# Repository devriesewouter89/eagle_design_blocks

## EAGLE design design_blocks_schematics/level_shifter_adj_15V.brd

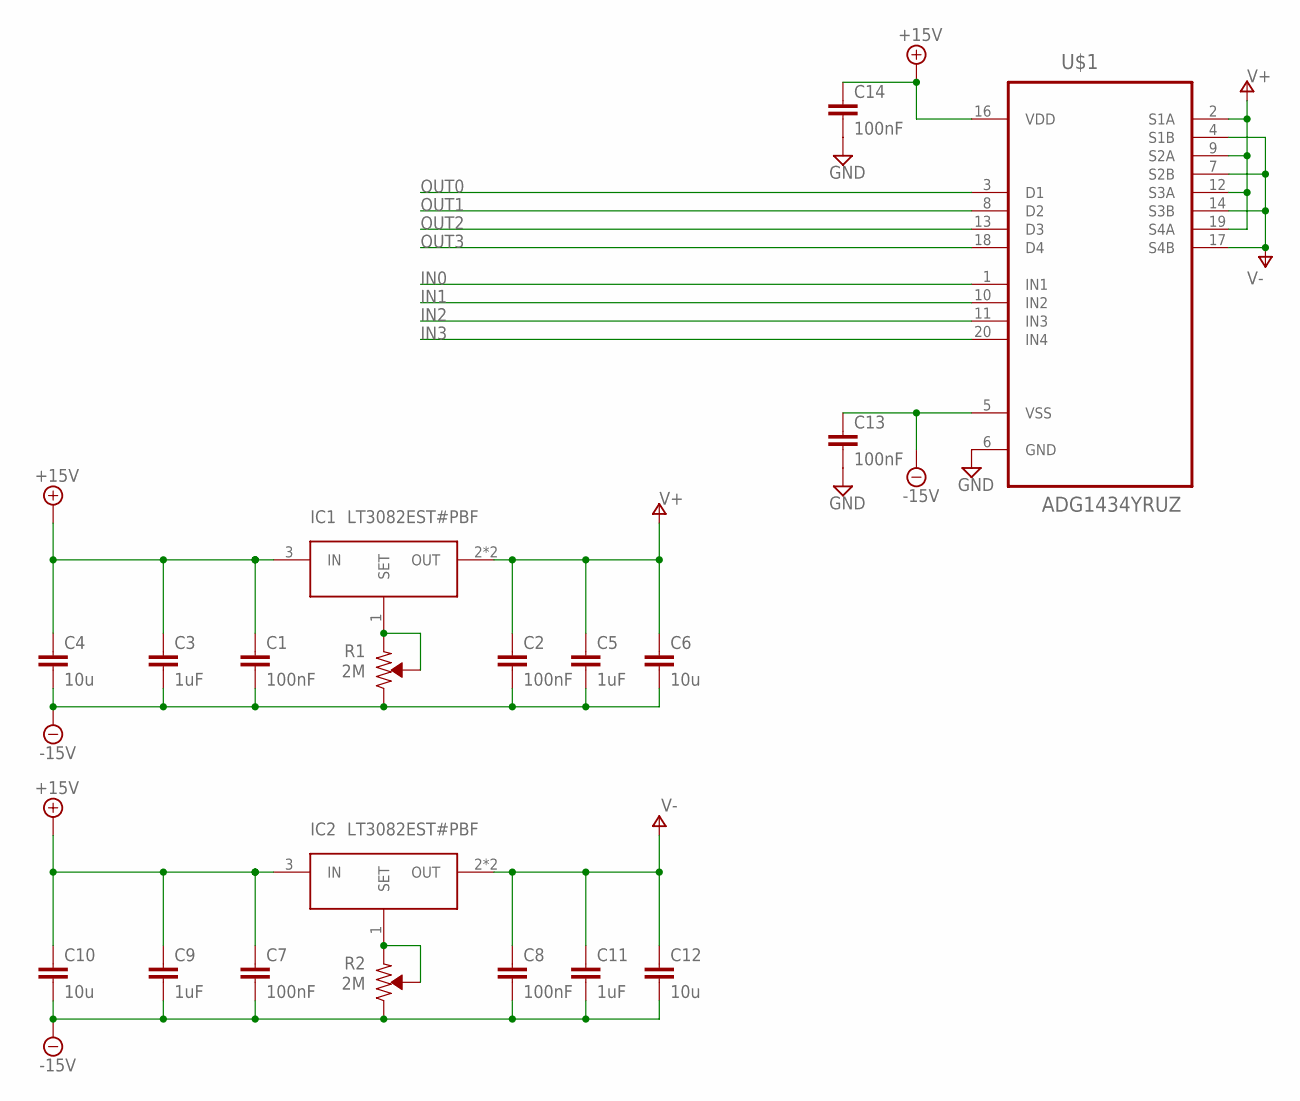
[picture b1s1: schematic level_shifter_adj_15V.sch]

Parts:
C1, C2, C7, C8, C13, C14: 100nF; C0402
C3, C5, C9, C11: 1uF; C0402; VOLTAGERATING 25V
C4, C6, C10, C12: 10u; C0603; VOLTAGERATING 25V
IC1, IC2: LT3082EST#PBF; SOT230P700X180-4N
R1, R2: 2M; TRIM_3296Y-1-202LF
U$1: ADG1434YRUZ; SOP65P640X120-20N

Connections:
+15V: C1.1, C3.1, C4.1, C7.1, C9.1, C10.1, C14.1, IC1.3 (IN), IC2.3 (IN), U$1.16 (VDD)
-15V: C1.2, C2.2, C3.2, C4.2, C5.2, C6.2, C7.2, C8.2, C9.2, C10.2, C11.2, C12.2, C13.1, R1.3 (CW), R2.3 (CW), U$1.5 (VSS)
GND: C13.2, C14.2, U$1.6 (GND)
IN0: U$1.1 (IN1)
IN1: U$1.10 (IN2)
IN2: U$1.11 (IN3)
IN3: U$1.20 (IN4)
unnamed: IC2.1 (SET), R2.1 (CCW), R2.2 (WIPER)
unnamed: IC1.1 (SET), R1.1 (CCW), R1.2 (WIPER)
OUT0: U$1.3 (D1)
OUT1: U$1.8 (D2)
OUT2: U$1.13 (D3)
OUT3: U$1.18 (D4)
V+: C2.1, C5.1, C6.1, IC1.2 (OUT), IC1.4 (OUT), U$1.2 (S1A), U$1.9 (S2A), U$1.12 (S3A), U$1.19 (S4A)
V-: C8.1, C11.1, C12.1, IC2.2 (OUT), IC2.4 (OUT), U$1.4 (S1B), U$1.7 (S2B), U$1.14 (S3B), U$1.17 (S4B)

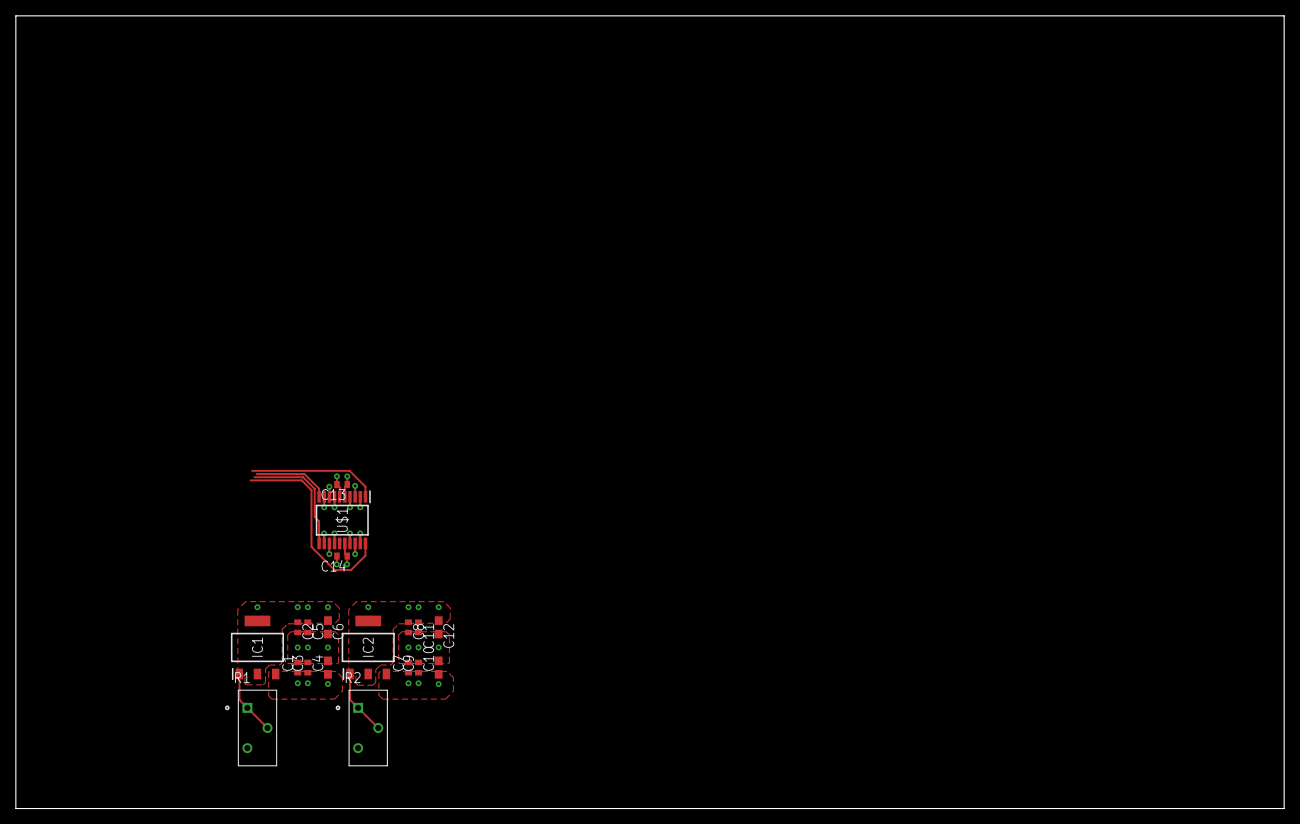
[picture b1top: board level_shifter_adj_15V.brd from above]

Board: 2 copper layers, 160.0 x 100.0 mm, 19 parts (0 on the bottom side), 7 nets.

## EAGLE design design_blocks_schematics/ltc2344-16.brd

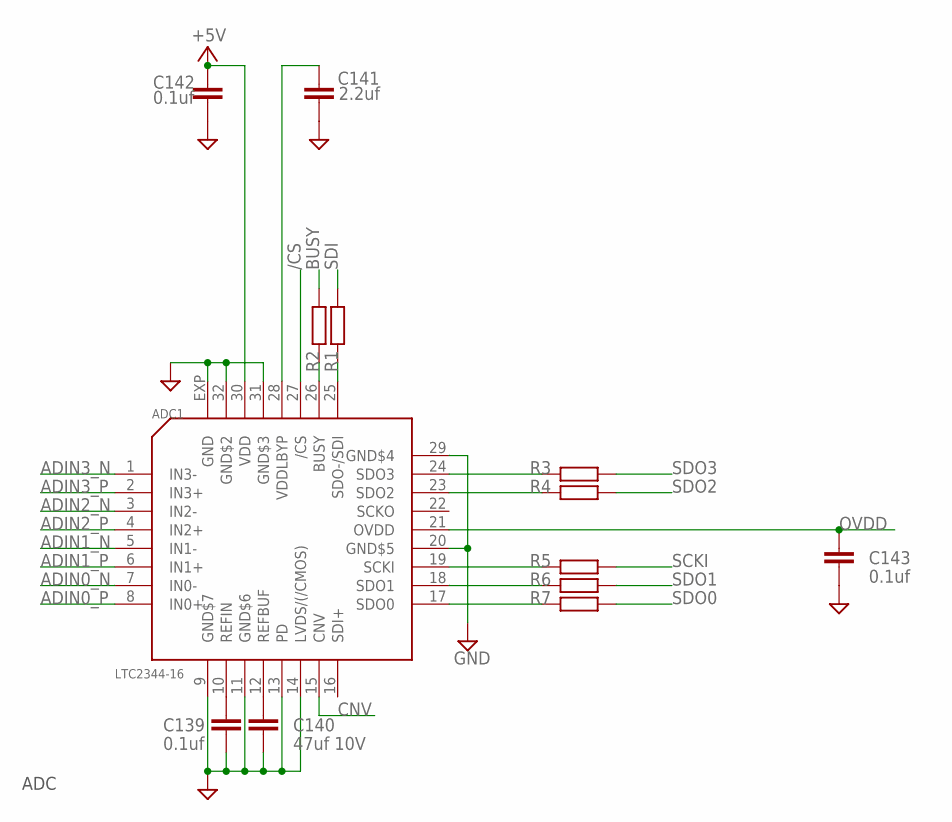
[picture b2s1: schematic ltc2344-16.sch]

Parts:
ADC1: LTC2344-16; QFN32
C139, C142, C143: 0.1uf; C0402
C140: 47uf 10V; C1210
C141: 2.2uf; C0402
R1, R2, R3, R4, R5, R6, R7: 33R; R0402

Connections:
+5V: ADC1.30 (VDD), C142.1
/CS: ADC1.27 (/CS)
ADIN0_N: ADC1.7 (IN0-)
ADIN0_P: ADC1.8 (IN0+)
ADIN1_N: ADC1.5 (IN1-)
ADIN1_P: ADC1.6 (IN1+)
ADIN2_N: ADC1.3 (IN2-)
ADIN2_P: ADC1.4 (IN2+)
ADIN3_N: ADC1.1 (IN3-)
ADIN3_P: ADC1.2 (IN3+)
BUSY: R2.2
CNV: ADC1.15 (CNV)
GND: ADC1.9 (GND$7), ADC1.11 (GND$6), ADC1.13 (PD), ADC1.14 (LVDS/(/CMOS)), ADC1.20 (GND$5), ADC1.29 (GND$4), ADC1.31 (GND$3), ADC1.32 (GND$2), ADC1.EXP (GND), C139.2, C140.2, C141.2, C142.2, C143.2
N1: ADC1.26 (BUSY), R2.1
N2: ADC1.25 (SDO-/SDI), R1.1
unnamed: ADC1.24 (SDO3), R3.2
unnamed: ADC1.23 (SDO2), R4.2
unnamed: ADC1.19 (SCKI), R5.2
unnamed: ADC1.18 (SDO1), R6.2
unnamed: ADC1.17 (SDO0), R7.2
unnamed: ADC1.10 (REFIN), C139.1
unnamed: ADC1.12 (REFBUF), C140.1
unnamed: ADC1.28 (VDDLBYP), C141.1
OVDD: ADC1.21 (OVDD), C143.1
SCKI: R5.1
SDI: R1.2
SDO0: R7.1
SDO1: R6.1
SDO2: R4.1
SDO3: R3.1

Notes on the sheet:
ADC

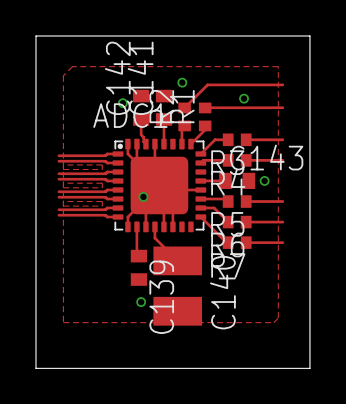
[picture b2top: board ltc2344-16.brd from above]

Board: 4 copper layers, 15.2 x 18.5 mm, 13 parts (0 on the bottom side), 13 nets.

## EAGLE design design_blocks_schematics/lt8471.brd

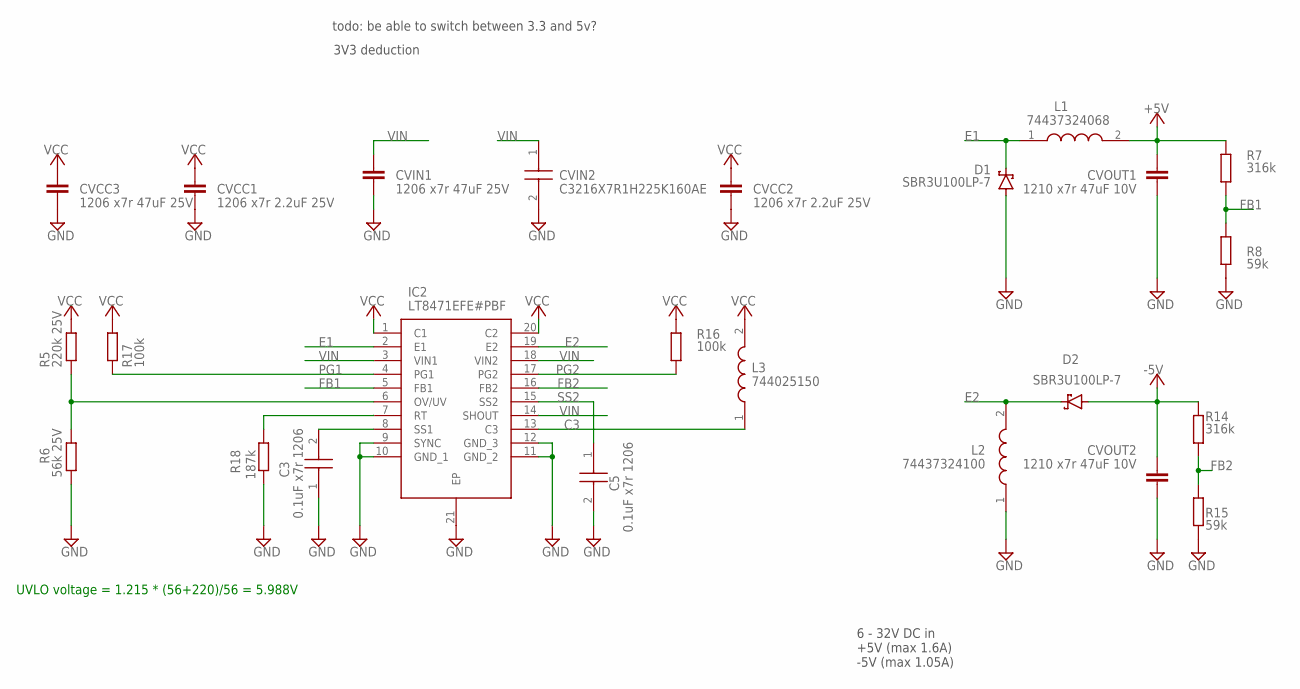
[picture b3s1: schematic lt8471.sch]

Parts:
C3, C5: 0.1uF x7r 1206; CAPC3416X90N
CVCC1, CVCC2: 1206 x7r 2.2uF 25V; C1206
CVCC3: 1206 x7r 47uF 25V; C1210
CVIN1: 1206 x7r 47uF 25V; C1210
CVIN2: C3216X7R1H225K160AE; CAPC3216X180N
CVOUT1, CVOUT2: 1210 x7r 47uF 10V; C1210
D1, D2: SBR3U100LP-7; SBR3U100LP7
IC2: LT8471EFE#PBF; SOP65P640X120-21N
L1: 74437324068; WE-LHMI_402048
L2: 74437324100; WE-LHMI_402048
L3: 744025150; WE-TPC_282892
R5: 220k 25V; M1206
R6: 56k 25V; M1206
R7, R14: 316k; R1206
R8, R15: 59k; R1206
R16, R17: 100k; R1206
R18: 187k; R1206

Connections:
+5V: CVOUT1.2, L1.2, R7.2
-5V: CVOUT2.2, D2.1 (A), D2.2 (A), D2.3 (A), D2.4 (A), R14.2
C3: IC2.13 (C3), L3.1
E1: D1.5 (C), IC2.2 (E1), L1.1
E2: D2.5 (C), IC2.19 (E2), L2.2
FB1: IC2.5 (FB1), R7.1, R8.2
FB2: IC2.16 (FB2), R14.1, R15.2
GND: C3.1, C5.2, CVCC1.2, CVCC2.1, CVCC3.1, CVIN1.2, CVIN2.2, CVOUT1.1, CVOUT2.1, D1.1 (A), D1.2 (A), D1.3 (A), D1.4 (A), IC2.9 (SYNC), IC2.10 (GND_1), IC2.11 (GND_2), IC2.12 (GND_3), IC2.21 (EP), L2.1, R6.1, R8.1, R15.1, R18.2
unnamed: IC2.7 (RT), R18.1
unnamed: IC2.6 (OV/UV), R5.1, R6.2
PG1: IC2.4 (PG1), R17.1
PG2: IC2.17 (PG2), R16.2
SS1: C3.2, IC2.8 (SS1)
SS2: C5.1, IC2.15 (SS2)
VCC: CVCC1.1, CVCC2.2, CVCC3.2, IC2.1 (C1), IC2.20 (C2), L3.2, R5.2, R16.1, R17.2
VIN: CVIN1.1, CVIN2.1, IC2.3 (VIN1), IC2.14 (SHOUT), IC2.18 (VIN2)

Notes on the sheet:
3V3 deduction
todo: be able to switch between 3.3 and 5v?
6 - 32V DC in +5V (max 1.6A) -5V (max 1.05A)
UVLO voltage = 1.215 * (56+220)/56 = 5.988V

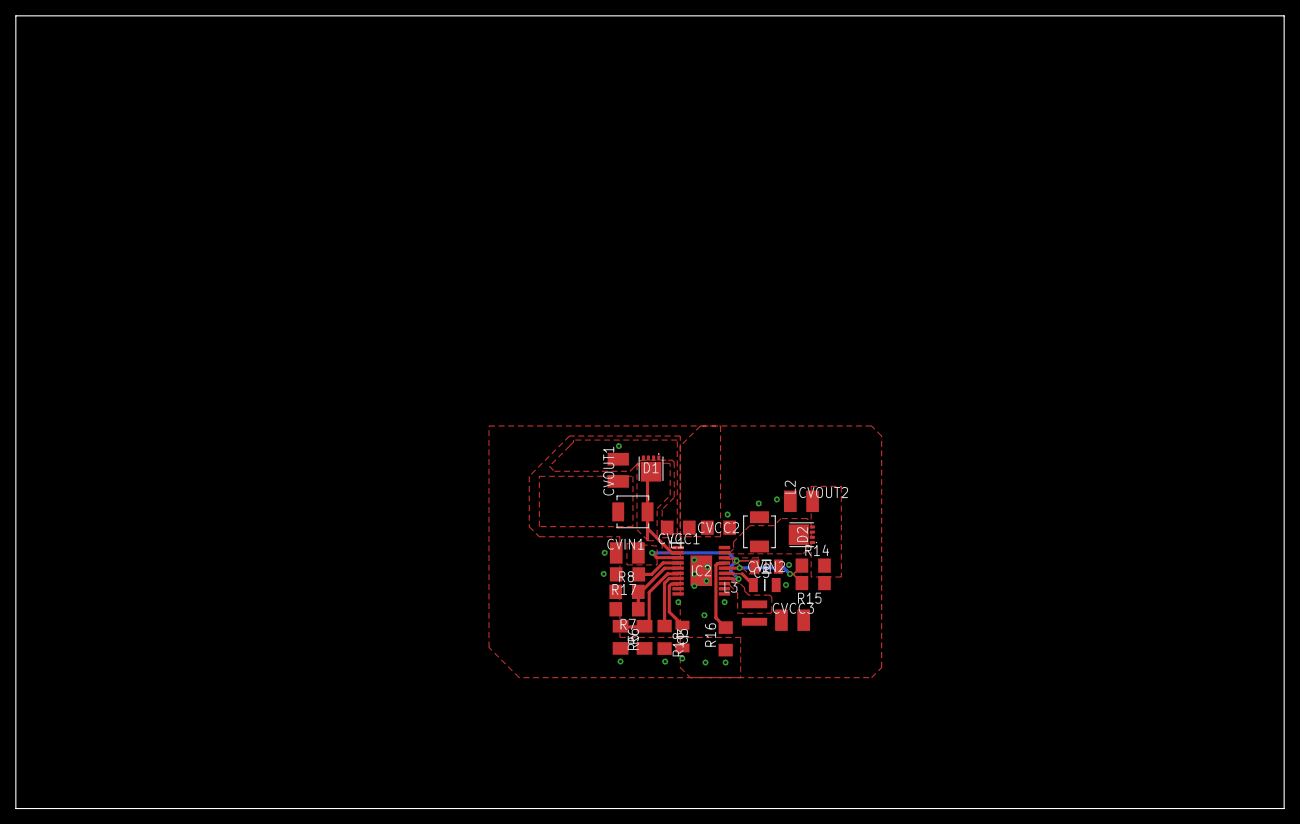
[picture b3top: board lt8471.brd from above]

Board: 2 copper layers, 160.0 x 100.0 mm, 24 parts (0 on the bottom side), 16 nets.

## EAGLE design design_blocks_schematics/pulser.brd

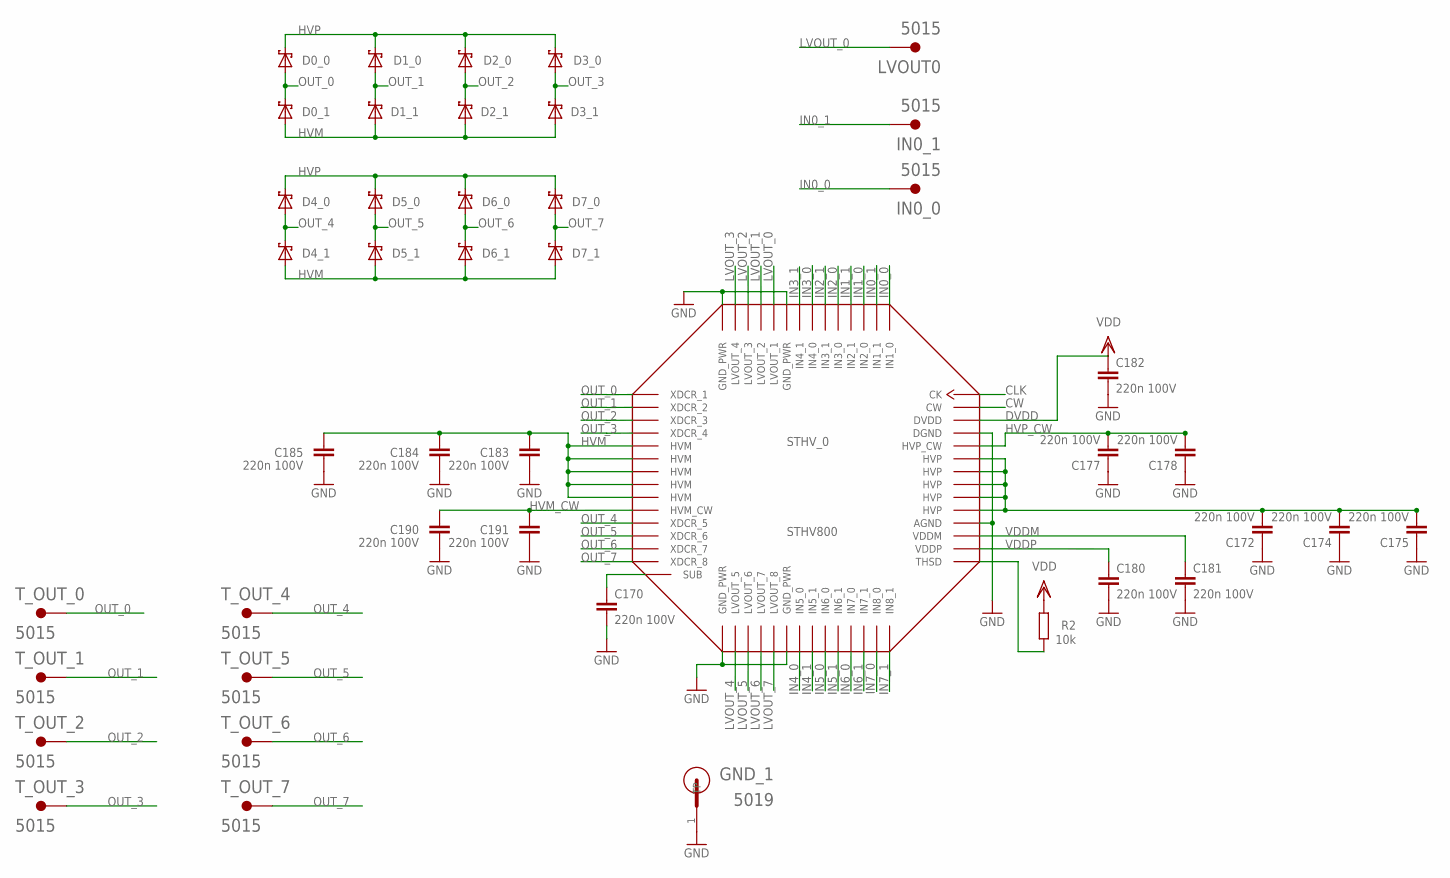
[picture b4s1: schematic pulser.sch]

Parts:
C170, C172, C174, C175, C177, C178, C180, C181, C182, C183, C184, C185, C190, C191: 220n 100V; C0805
D0_0, D0_1, D1_0, D1_1, D2_0, D2_1, D3_0, D3_1, D4_0, D4_1, D5_0, D5_1, D6_0, D6_1, D7_0, D7_1: SBR1U200P1SBR1U200P1; POWERDI-123
GND_1: 5019; TP380X203
IN0_0, IN0_1: 5015; KEYSTONE_5015
LVOUT0: 5015; KEYSTONE_5015
R2: 10k; R0805
STHV_0: STHV800; TFLGA-56LD
T_OUT_0, T_OUT_1, T_OUT_2, T_OUT_3, T_OUT_4, T_OUT_5, T_OUT_6, T_OUT_7: 5015; KEYSTONE_5015

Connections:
CLK: STHV_0.CK
CW: STHV_0.CW
GND: C170.2, C172.1, C174.1, C175.1, C177.1, C178.1, C180.2, C181.2, C182.2, C183.2, C184.2, C185.2, C190.1, C191.1, GND_1.1, STHV_0.AGND, STHV_0.DGND, STHV_0.GND_PWR@1 (GND_PWR), STHV_0.GND_PWR@2 (GND_PWR), STHV_0.GND_PWR@3 (GND_PWR), STHV_0.GND_PWR@4 (GND_PWR)
HVM: C183.1, C184.1, C185.1, D0_1.A, D1_1.A, D2_1.A, D3_1.A, D4_1.A, D5_1.A, D6_1.A, D7_1.A, STHV_0.HVM@1 (HVM), STHV_0.HVM@2 (HVM), STHV_0.HVM@3 (HVM), STHV_0.HVM@4 (HVM), STHV_0.HVM@5 (HVM)
HVM_CW: C190.2, C191.2, STHV_0.HVM_CW
HVP: C172.2, C174.2, C175.2, D0_0.C, D1_0.C, D2_0.C, D3_0.C, D4_0.C, D5_0.C, D6_0.C, D7_0.C, STHV_0.HVP@1 (HVP), STHV_0.HVP@2 (HVP), STHV_0.HVP@3 (HVP), STHV_0.HVP@4 (HVP), STHV_0.HVP@5 (HVP)
HVP_CW: C177.2, C178.2, STHV_0.HVP_CW
IN0_0: IN0_0.1, STHV_0.IN1_0
IN0_1: IN0_1.1, STHV_0.IN1_1
IN1_0: STHV_0.IN2_0
IN1_1: STHV_0.IN2_1
IN2_0: STHV_0.IN3_0
IN2_1: STHV_0.IN3_1
IN3_0: STHV_0.IN4_0
IN3_1: STHV_0.IN4_1
IN4_0: STHV_0.IN5_0
IN4_1: STHV_0.IN5_1
IN5_0: STHV_0.IN6_0
IN5_1: STHV_0.IN6_1
IN6_0: STHV_0.IN7_0
IN6_1: STHV_0.IN7_1
IN7_0: STHV_0.IN8_0
IN7_1: STHV_0.IN8_1
LVOUT_0: LVOUT0.1, STHV_0.LVOUT_1
LVOUT_1: STHV_0.LVOUT_2
LVOUT_2: STHV_0.LVOUT_3
LVOUT_3: STHV_0.LVOUT_4
LVOUT_4: STHV_0.LVOUT_5
LVOUT_5: STHV_0.LVOUT_6
LVOUT_6: STHV_0.LVOUT_7
LVOUT_7: STHV_0.LVOUT_8
unnamed: R2.1, STHV_0.THSD
unnamed: C170.1, STHV_0.SUB
OUT_0: D0_0.A, D0_1.C, STHV_0.XDCR_1, T_OUT_0.1
OUT_1: D1_0.A, D1_1.C, STHV_0.XDCR_2, T_OUT_1.1
OUT_2: D2_0.A, D2_1.C, STHV_0.XDCR_3, T_OUT_2.1
OUT_3: D3_0.A, D3_1.C, STHV_0.XDCR_4, T_OUT_3.1
OUT_4: D4_0.A, D4_1.C, STHV_0.XDCR_5, T_OUT_4.1
OUT_5: D5_0.A, D5_1.C, STHV_0.XDCR_6, T_OUT_5.1
OUT_6: D6_0.A, D6_1.C, STHV_0.XDCR_7, T_OUT_6.1
OUT_7: D7_0.A, D7_1.C, STHV_0.XDCR_8, T_OUT_7.1
VDDM: C181.1, STHV_0.VDDM

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
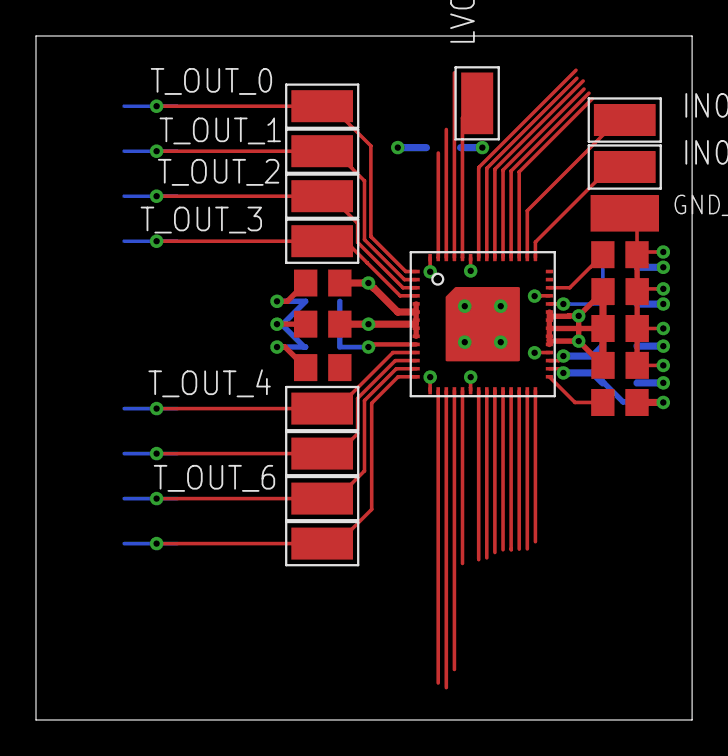
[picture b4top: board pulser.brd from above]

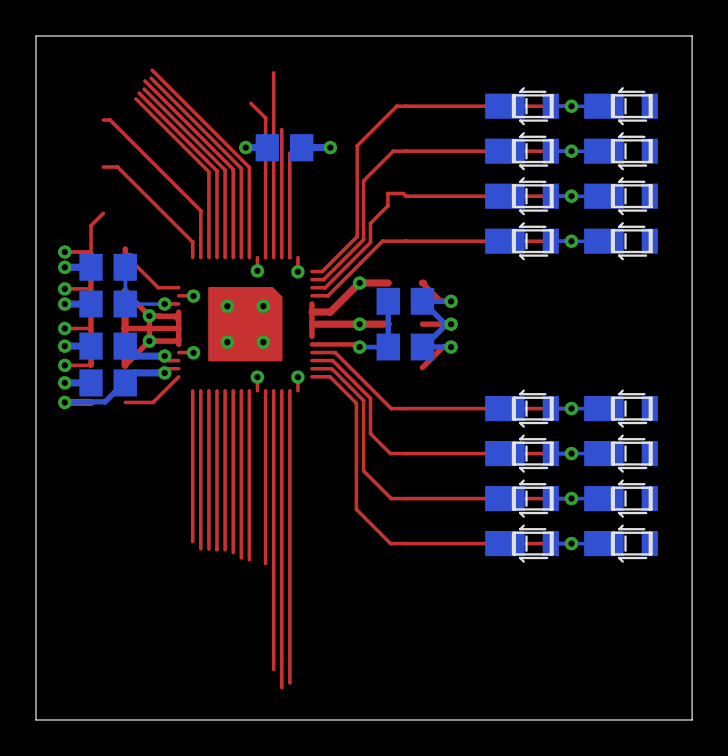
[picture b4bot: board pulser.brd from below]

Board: 2 copper layers, 36.5 x 38.0 mm, 44 parts (23 on the bottom side), 20 nets.

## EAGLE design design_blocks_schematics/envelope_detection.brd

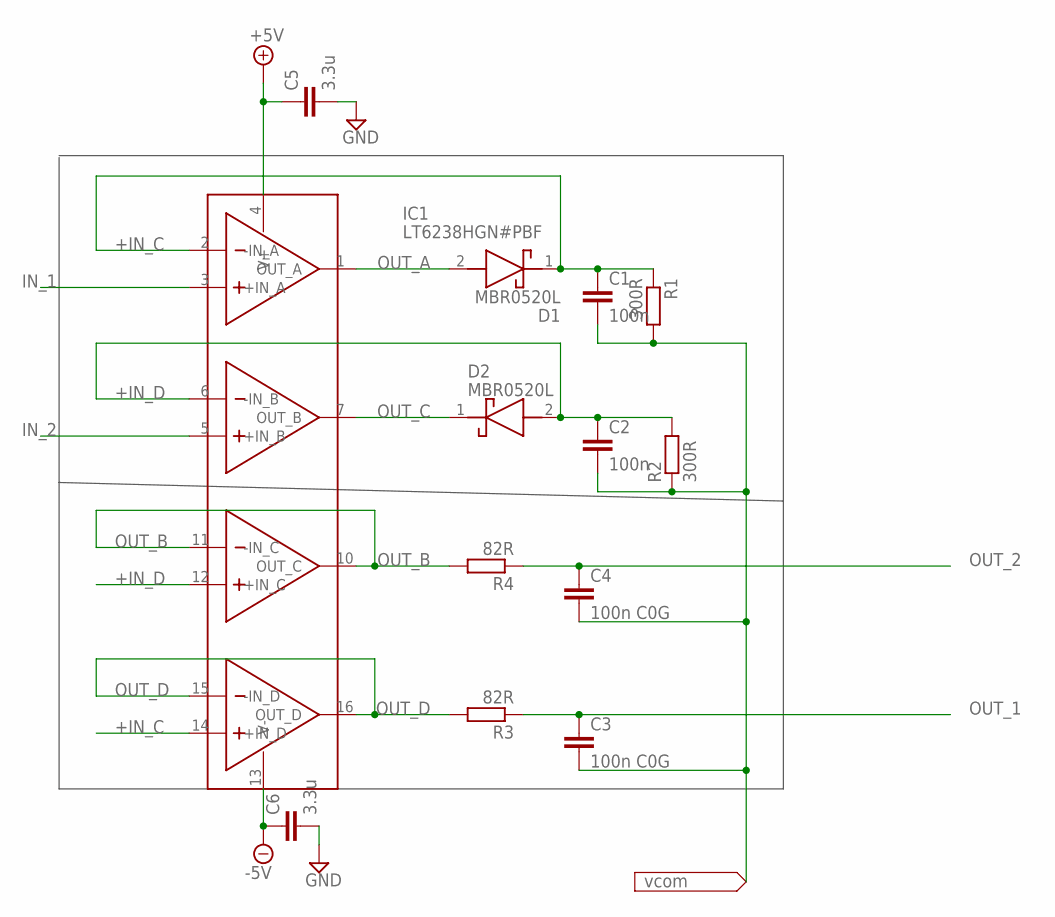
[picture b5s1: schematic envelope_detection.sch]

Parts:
C1, C2: 100n; C0603
C3, C4: 100n C0G; C1206
C5, C6: 3.3u; C0402
D1, D2: MBR0520L; SOD3816X128N
IC1: LT6238HGN#PBF; SOP64P601X175-16N
R1, R2: 300R; M0805
R3, R4: 82R; M0805

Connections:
+5V: C5.1, IC1.4 (V+)
+IN_C: C1.1, D1.1 (K), IC1.2 (-IN_A), IC1.14 (+IN_D), R1.1
+IN_D: C2.1, D2.2 (A), IC1.6 (-IN_B), IC1.12 (+IN_C), R2.2
-5V: C6.1, IC1.13 (V-)
GND: C5.2, C6.2
IN_1: IC1.3 (+IN_A)
IN_2: IC1.5 (+IN_B)
OUT_1: C3.1, R3.1
OUT_2: C4.1, R4.1
OUT_A: D1.2 (A), IC1.1 (OUT_A)
OUT_B: IC1.10 (OUT_C), IC1.11 (-IN_C), R4.2
OUT_C: D2.1 (K), IC1.7 (OUT_B)
OUT_D: IC1.15 (-IN_D), IC1.16 (OUT_D), R3.2
VCOM: C1.2, C2.2, C3.2, C4.2, R1.2, R2.1

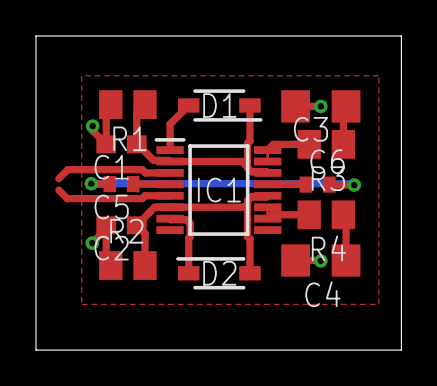
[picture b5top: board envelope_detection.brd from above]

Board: 2 copper layers, 20.3 x 17.4 mm, 13 parts (0 on the bottom side), 12 nets.

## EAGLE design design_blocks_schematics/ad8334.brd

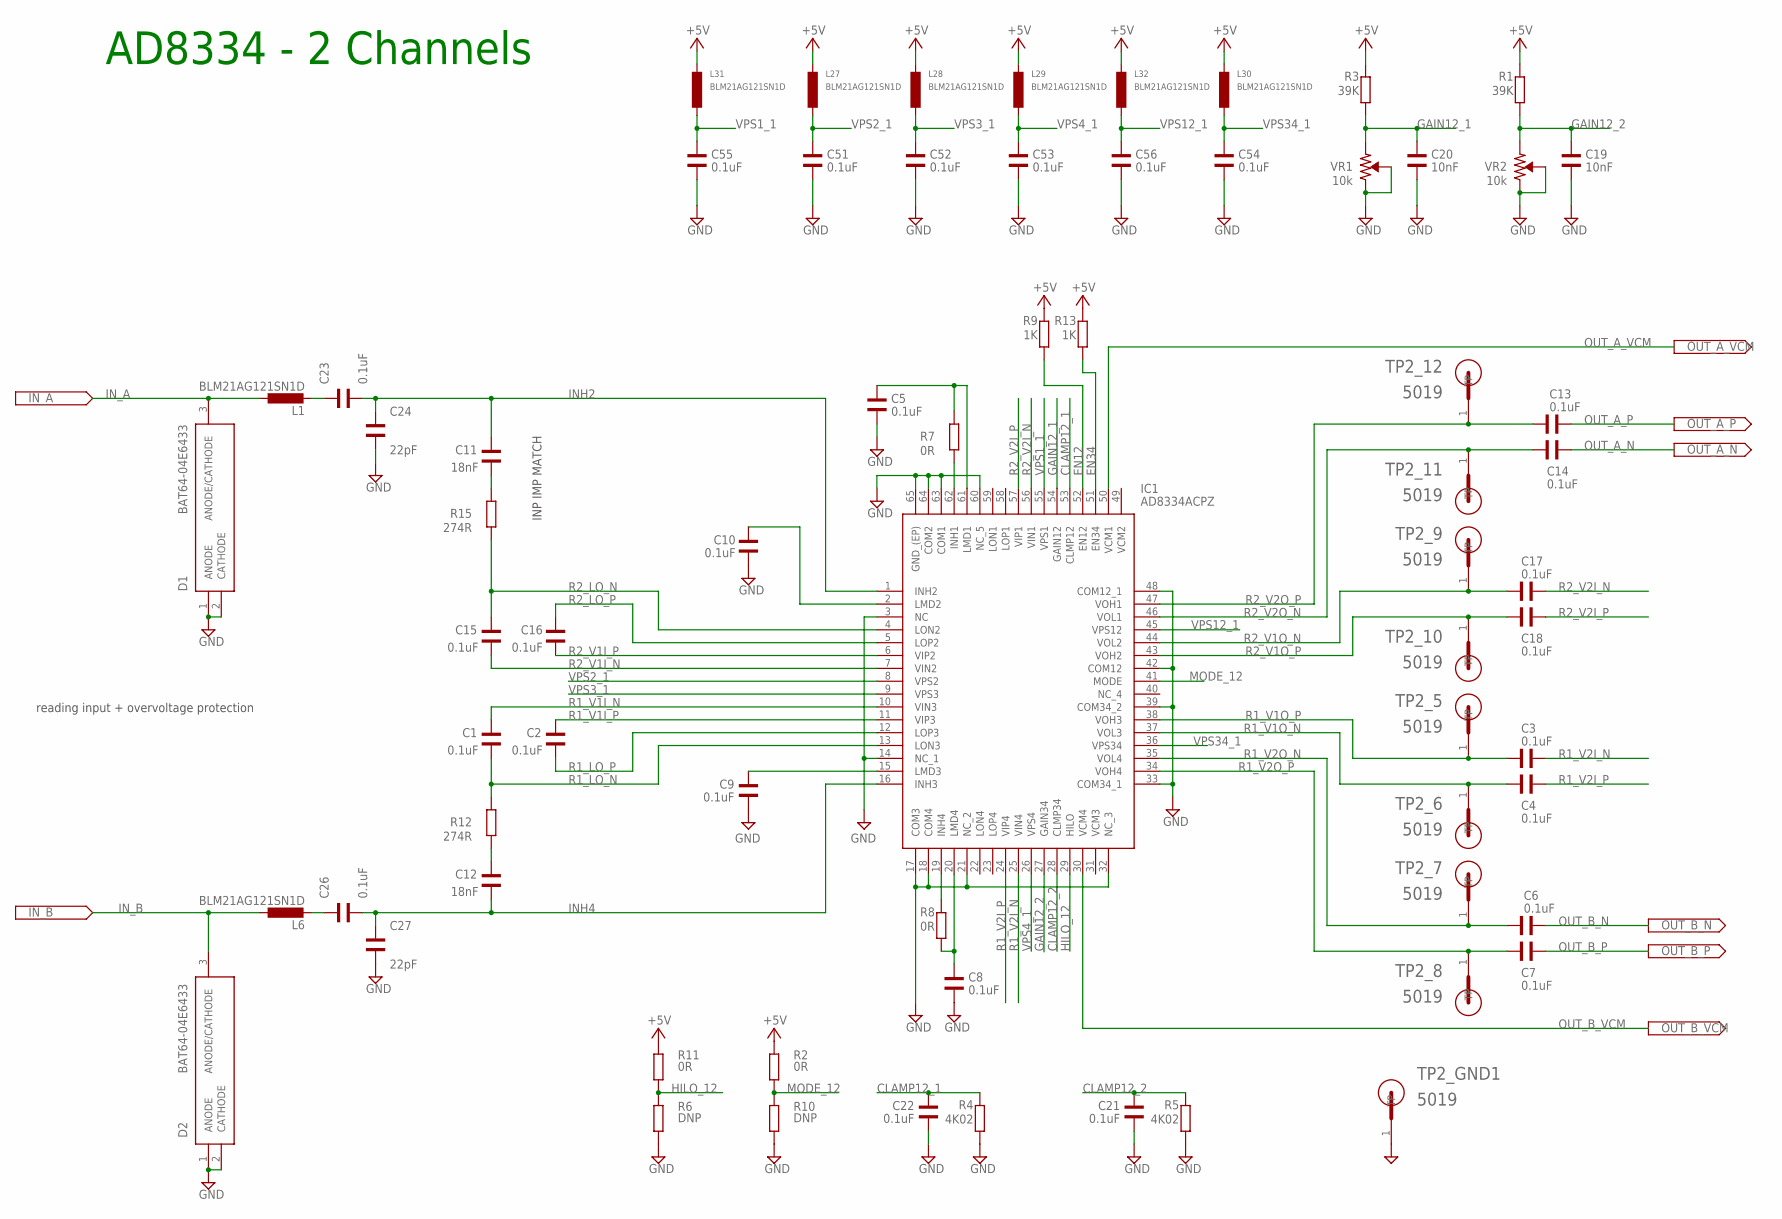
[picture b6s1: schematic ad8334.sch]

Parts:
C1, C2, C3, C4, C5, C6, C7, C8, C9, C10, C13, C14, C15, C16, C17, C18, C21, C22, C23, C26, C51, C52, C53, C54, C55, C56: 0.1uF; WCAP-CSGP_0402
C11, C12: 18nF; WCAP-CSGP_0402
C19, C20: 10nF; WCAP-CSGP_0402
C24, C27: 22pF; WCAP-CSGP_0402
D1, D2: BAT64-04E6433; SOT95P260X110-3N
IC1: AD8334ACPZ; QFN50P900X900X100-65N
L1, L6, L27, L28, L29, L30, L31, L32: BLM21AG121SN1D; L2012C
R1, R3: 39K; R0402
R2, R7, R8, R11: 0R; R0402
R4, R5: 4K02; R0402
R6, R10: DNP; R0402
R9, R13: 1K; R0402
R12, R15: 274R; R0402
TP2_5, TP2_6, TP2_7, TP2_8, TP2_9, TP2_10, TP2_11, TP2_12, TP2_GND1: 5019; TP380X203
VR1, VR2: 10k; TRIMPOT-SMD-TC33X

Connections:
+5V: L27.1, L28.1, L29.1, L30.1, L31.1, L32.1, R1.2, R2.2, R3.2, R9.2, R11.2, R13.2
CLAMP12_1: C22.1, IC1.53 (CLMP12), R4.2
CLAMP12_2: C21.1, IC1.28 (CLMP34), R5.2
EN12: IC1.52 (EN12), R9.1
EN34: IC1.51 (EN34), R13.1
GAIN12_1: C20.1, IC1.54 (GAIN12), R3.1, VR1.3 (CCW)
GAIN12_2: C19.1, IC1.27 (GAIN34), R1.1, VR2.3 (CCW)
GND: C5.2, C8.1, C9.1, C10.1, C19.2, C20.2, C21.2, C22.2, C24.1, C27.1, C51.1, C52.1, C53.1, C54.1, C55.1, C56.1, D1.1 (ANODE), D1.2 (CATHODE), D2.1 (ANODE), D2.2 (CATHODE), IC1.3 (NC), IC1.14 (NC_1), IC1.17 (COM3), IC1.18 (COM4), IC1.21 (NC_2), IC1.32 (NC_3), IC1.60 (NC_5), IC1.63 (COM1), IC1.64 (COM2), IC1.65 (GND_(EP)), R4.1, R5.1, R6.1, R10.1, TP2_GND1.1, VR1.1 (CW), VR1.2 (WIPER), VR2.1 (CW), VR2.2 (WIPER)
HILO_12: IC1.29 (HILO), R6.2, R11.1
INH2: C11.2, C23.1, C24.2, IC1.1 (INH2)
INH4: C12.1, C26.1, C27.2, IC1.16 (INH3)
IN_A: D1.3 (ANODE/CATHODE), L1.1
IN_B: D2.3 (ANODE/CATHODE), L6.1
MODE_12: IC1.41 (MODE), R2.1, R10.2
unnamed: C5.1, IC1.61 (LMD1), R7.2
unnamed: C8.2, IC1.20 (LMD4), R8.1
unnamed: IC1.33 (COM34_1), IC1.39 (COM34_2), IC1.42 (COM12), IC1.48 (COM12_1)
unnamed: C10.2, IC1.2 (LMD2)
unnamed: C9.2, IC1.15 (LMD3)
unnamed: C23.2, L1.2
unnamed: C11.1, R15.2
unnamed: C26.2, L6.2
unnamed: C12.2, R12.1
unnamed: IC1.19 (INH4), R8.2
OUT_A_N: C14.2
OUT_A_P: C13.2
OUT_A_VCM: IC1.50 (VCM1)
OUT_B_N: C6.2
OUT_B_P: C7.2
OUT_B_VCM: IC1.30 (VCM4)
R1_I: IC1.62 (INH1), R7.1
R1_LO_N: C1.1, IC1.13 (LON3), R12.2
R1_LO_P: C2.1, IC1.12 (LOP3)
R1_V1I_N: C1.2, IC1.10 (VIN3)
R1_V1I_P: C2.2, IC1.11 (VIP3)
R1_V1O_N: C4.1, IC1.37 (VOL3), TP2_6.1
R1_V1O_P: C3.1, IC1.38 (VOH3), TP2_5.1
R1_V2I_N: C3.2, IC1.25 (VIN4)
R1_V2I_P: C4.2, IC1.24 (VIP4)
R1_V2O_N: C6.1, IC1.35 (VOL4), TP2_7.1
R1_V2O_P: C7.1, IC1.34 (VOH4), TP2_8.1
R2_LO_N: C15.2, IC1.4 (LON2), R15.1
R2_LO_P: C16.2, IC1.5 (LOP2)
R2_V1I_N: C15.1, IC1.7 (VIN2)
R2_V1I_P: C16.1, IC1.6 (VIP2)
R2_V1O_N: C17.1, IC1.44 (VOL2), TP2_9.1
R2_V1O_P: C18.1, IC1.43 (VOH2), TP2_10.1
R2_V2I_N: C17.2, IC1.56 (VIN1)
R2_V2I_P: C18.2, IC1.57 (VIP1)
R2_V2O_N: C14.1, IC1.46 (VOL1), TP2_11.1
R2_V2O_P: C13.1, IC1.47 (VOH1), TP2_12.1
VPS1_1: C55.2, IC1.55 (VPS1), L31.2
VPS2_1: C51.2, IC1.8 (VPS2), L27.2
VPS3_1: C52.2, IC1.9 (VPS3), L28.2
VPS4_1: C53.2, IC1.26 (VPS4), L29.2
VPS12_1: C56.2, IC1.45 (VPS12), L32.2
VPS34_1: C54.2, IC1.36 (VPS34), L30.2

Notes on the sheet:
INP IMP MATCH
reading input + overvoltage protection
AD8334 - 2 Channels

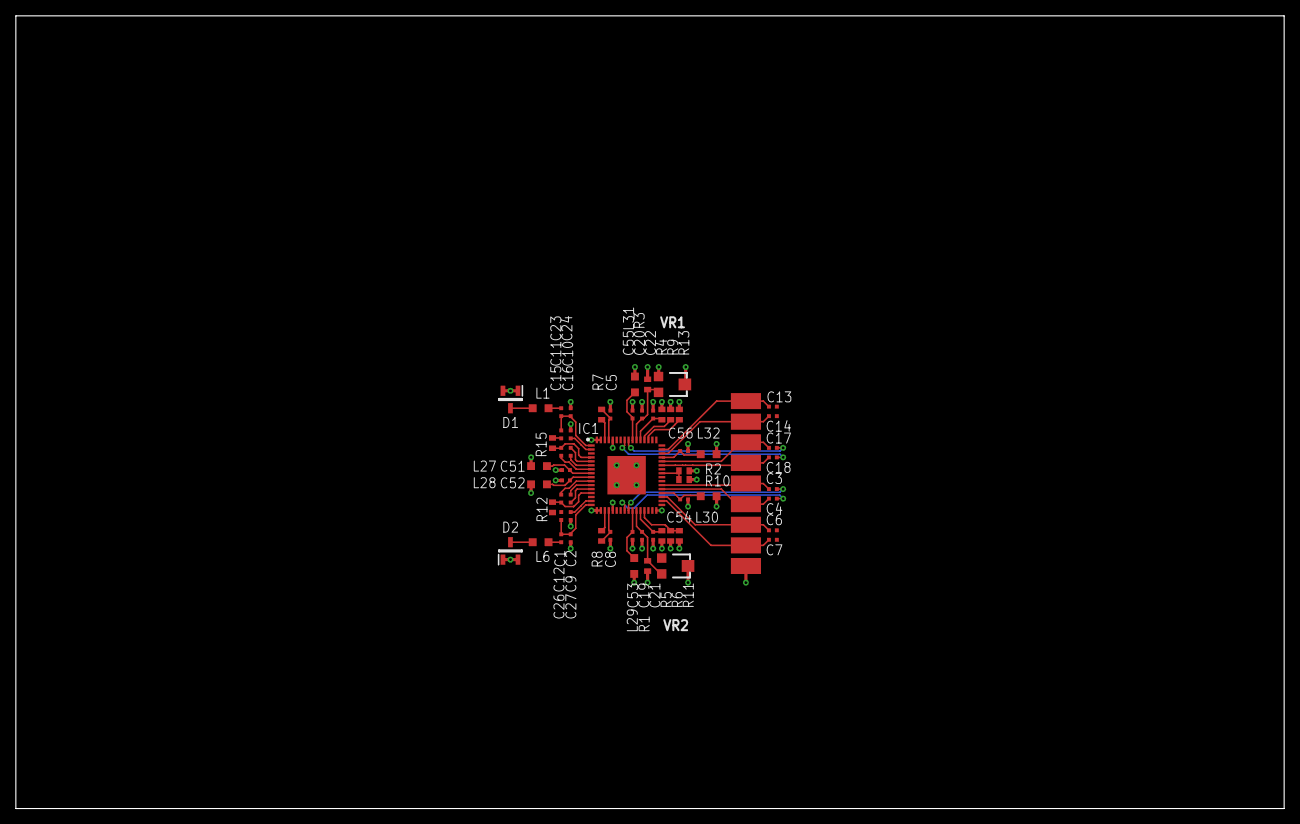
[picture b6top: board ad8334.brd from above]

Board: 2 copper layers, 160.0 x 100.0 mm, 68 parts (0 on the bottom side), 51 nets.

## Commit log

2019-10-18 added design blocks of previous silense repo
2019-10-22 Added schematic and layout for the level shifter

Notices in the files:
parts and their libraries:
Wurth_Elektronik_Passive_Capacitors_rev1: Copyright: Würth Elektronik
SparkFun-Resistors: Licensing: Creative Commons ShareAlike 4.0 International - https://creativecommons.org/licenses/by-sa/4.0
